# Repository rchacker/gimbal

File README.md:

gimbal
=======

Gimbal forked from _BruGi

Aim is to have a very simple 8 bit gimbal for which basic parameters are adjustable in the field without needing a computer.

*Agouti Prototype*

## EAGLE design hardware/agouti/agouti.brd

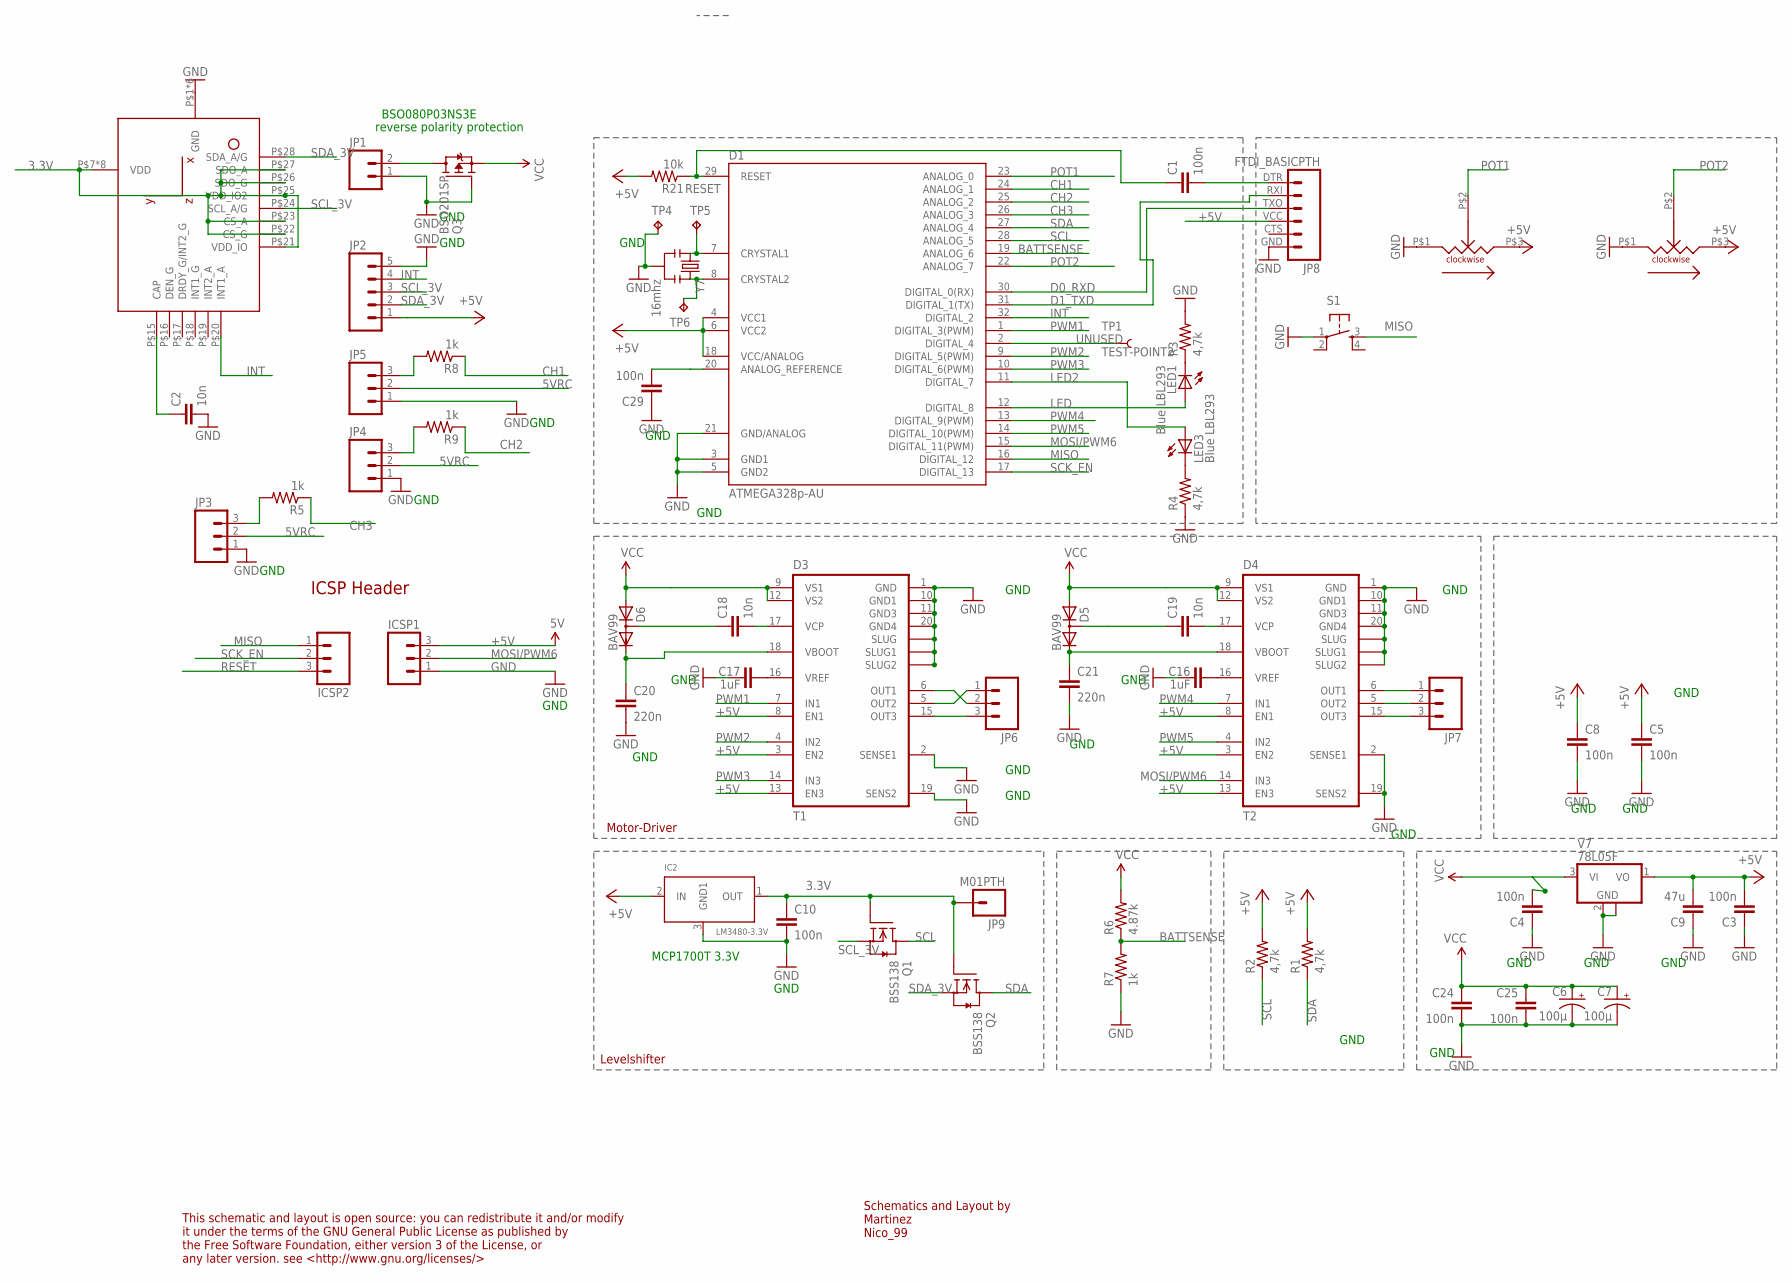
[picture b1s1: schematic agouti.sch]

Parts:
C1, C3, C4, C5, C8, C10, C24, C25, C29: 100n; 0805
C2, C18, C19: 10n; 0805
C6, C7: 100µ; PANASONIC_D
C9: 47u; C1210
C16, C17: 1uF; 0805
C20, C21: 220n; 0805
D1: ATMEGA328p-AU; TQFP32-08
D3: T1; SO20POWER2
D4: T2; SO20POWER2
D5, D6: BAV99; SOT23
IC2: LM3480-3.3V; SOT23
ICSP1, ICSP2: M03PTH; 1X03
JP1: M02PTH; 1X02
JP2: M05PTH; 1X05
JP3, JP4, JP5, JP6, JP7: M03PTH; 1X03
JP8: FTDI_BASICPTH; FTDI_BASIC
JP9: M01PTH; 1X01
LED1, LED3: Blue LBL293; CHIP-LED0603
Q1, Q2: BSS138; SOT23
Q3: BSO201SP; SO-8
R1, R2, R3, R4: 4,7k; 0805
R5, R7, R8, R9: 1k; 0805
R6: 4.87k; 0805
R21: 10k; 0805
S1: TAC_SWITCHSMD; TACTILE_SWITCH_SMD
TP1: TEST-POINT2; PAD.02X.02
TP4, TP5, TP6: TPTP06SQ; TP06SQ
U$3, U$5: TRIMMERPOT; BOURNES_3361P
U$6: LSM330; LGA-28
V7: 78L05F; SOT89
Y7: 16mhz; RESONATOR-SMD

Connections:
3.3V: C10.1, IC2.1 (OUT), JP9.1, Q1.1 (G), Q2.1 (G), U$6.P$7 (VDD), U$6.P$8 (VDD), U$6.P$9 (VDD), U$6.P$10 (VDD), U$6.P$11 (VDD), U$6.P$12 (VDD), U$6.P$13 (VDD), U$6.P$14 (VDD), U$6.P$21 (VDD_IO), U$6.P$22 (CS_G), U$6.P$23 (CS_A), U$6.P$25 (VDD_IO2), U$6.P$26 (SDO_G), U$6.P$27 (SDO_A)
5VRC: JP3.2, JP4.2, JP5.2
+5V: C3.2, C5.1, C8.1, C9.2, D1.4 (VCC1), D1.6 (VCC2), D1.18 (VCC/ANALOG), D3.3 (EN2), D3.8 (EN1), D3.13 (EN3), D4.3 (EN2), D4.8 (EN1), D4.13 (EN3), IC2.2 (IN), ICSP1.3, JP2.1, JP8.VCC (4), R1.2, R2.2, R21.2, U$3.P$3, U$5.P$3, V7.1 (VO)
BATTSENSE: D1.19 (ANALOG_6), R6.1, R7.2
CH1: D1.24 (ANALOG_1), R8.1
CH2: D1.25 (ANALOG_2), R9.1
CH3: D1.26 (ANALOG_3), R5.1
D0_RXD: D1.30 (DIGITAL_0(RX)), JP8.TXO (3)
D1_TXD: D1.31 (DIGITAL_1(TX)), JP8.RXI (2)
GND: C2.2, C3.1, C4.1, C5.2, C6.-, C7.-, C8.2, C9.1, C10.2, C16.1, C17.1, C20.2, C21.2, C24.2, C25.2, C29.1, D1.3 (GND1), D1.5 (GND2), D1.21 (GND/ANALOG), D3.1 (GND), D3.2 (SENSE1), D3.10 (GND1), D3.11 (GND3), D3.19 (SENS2), D3.20 (GND4), D3.SLUG (SLUG1), D3.SLUG1 (SLUG2), D3.SLUG2 (SLUG), D4.1 (GND), D4.2 (SENSE1), D4.10 (GND1), D4.11 (GND3), D4.19 (SENS2), D4.20 (GND4), D4.SLUG (SLUG1), D4.SLUG1 (SLUG2), D4.SLUG2 (SLUG), IC2.3 (GND1), ICSP1.1, JP1.1, JP2.5, JP3.1, JP4.1, JP5.1, JP8.GND (6), Q3.4 (G), R3.2, R4.1, R7.1, S1.1, TP4.TP, U$3.P$1, U$5.P$1, U$6.P$1 (GND), U$6.P$2 (GND), U$6.P$3 (GND), U$6.P$4 (GND), U$6.P$5 (GND), U$6.P$6 (GND), V7.2 (GND), V7.2@1 (GND), Y7.2
INT: D1.32 (DIGITAL_2), JP2.4, U$6.P$20 (INT1_A)
LED: D1.12 (DIGITAL_8), LED1.A
LED2: D1.11 (DIGITAL_7), LED3.A
MISO: D1.16 (DIGITAL_12), ICSP2.1, S1.3
MOSI/PWM6: D1.15 (DIGITAL_11(PWM)), D4.14 (IN3), ICSP1.2
unnamed: LED1.C, R3.1
unnamed: LED3.C, R4.2
unnamed: JP1.2, Q3.5 (D), Q3.6 (D), Q3.7 (D), Q3.8 (D)
unnamed: JP3.3, R5.2
unnamed: JP5.3, R8.2
unnamed: JP4.3, R9.2
unnamed: C16.2, D4.16 (VREF)
unnamed: C17.2, D3.16 (VREF)
unnamed: C1.2, JP8.DTR (1)
unnamed: C2.1, U$6.P$15 (CAP)
unnamed: C18.2, D3.17 (VCP)
unnamed: C19.2, D4.17 (VCP)
unnamed: C19.1, D5.3 (AC)
unnamed: C21.1, D4.18 (VBOOT), D5.2 (C)
unnamed: D3.15 (OUT3), JP6.3
unnamed: D4.6 (OUT1), JP7.1
unnamed: D4.5 (OUT2), JP7.2
unnamed: D4.15 (OUT3), JP7.3
unnamed: D3.5 (OUT2), JP6.1
unnamed: D3.6 (OUT1), JP6.2
unnamed: D1.8 (CRYSTAL2), TP6.TP, Y7.3
unnamed: D1.7 (CRYSTAL1), TP5.TP, Y7.1
unnamed: C29.2, D1.20 (ANALOG_REFERENCE)
POT1: D1.23 (ANALOG_0), U$3.P$2
POT2: D1.22 (ANALOG_7), U$5.P$2
PWM1: D1.1 (DIGITAL_3(PWM)), D3.7 (IN1)
PWM2: D1.9 (DIGITAL_5(PWM)), D3.4 (IN2)
PWM3: D1.10 (DIGITAL_6(PWM)), D3.14 (IN3)
PWM4: D1.13 (DIGITAL_9(PWM)), D4.7 (IN1)
PWM5: D1.14 (DIGITAL_10(PWM)), D4.4 (IN2)
RESET: C1.1, D1.29 (RESET), ICSP2.3, R21.1
SCK_EN: D1.17 (DIGITAL_13), ICSP2.2
SCL: D1.28 (ANALOG_5), Q1.3 (D), R2.1
SCL_3V: JP2.3, Q1.2 (S), U$6.P$24 (SCL_A/G)
SDA: D1.27 (ANALOG_4), Q2.3 (D), R1.1
SDA_3V: JP2.2, Q2.2 (S), U$6.P$28 (SDA_A/G)
UNUSED: D1.2 (DIGITAL_4), TP1.P$1
VBOOT1: C20.1, D3.18 (VBOOT), D6.2 (C)
VCC: C4.2, C6.+, C7.+, C24.1, C25.1, D3.9 (VS1), D3.12 (VS2), D4.9 (VS1), D4.12 (VS2), D5.1 (A), D6.1 (A), Q3.1 (S), Q3.2 (S), Q3.3 (S), R6.2, V7.3 (VI)
VCP1: C18.1, D6.3 (AC)

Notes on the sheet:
MCP1700T 3.3V
Motor-Driver
Levelshifter
This schematic and layout is open source: you can redistribute it and/or modify it under the terms of the GNU General Public License as published by the Free Software Foundation, either version 3 of the License, or any later version. see <http://www.gnu.org/licenses/>
Schematics and Layout by Martinez Nico_99
ICSP Header
GND
BSO080P03NS3E
reverse polarity protection

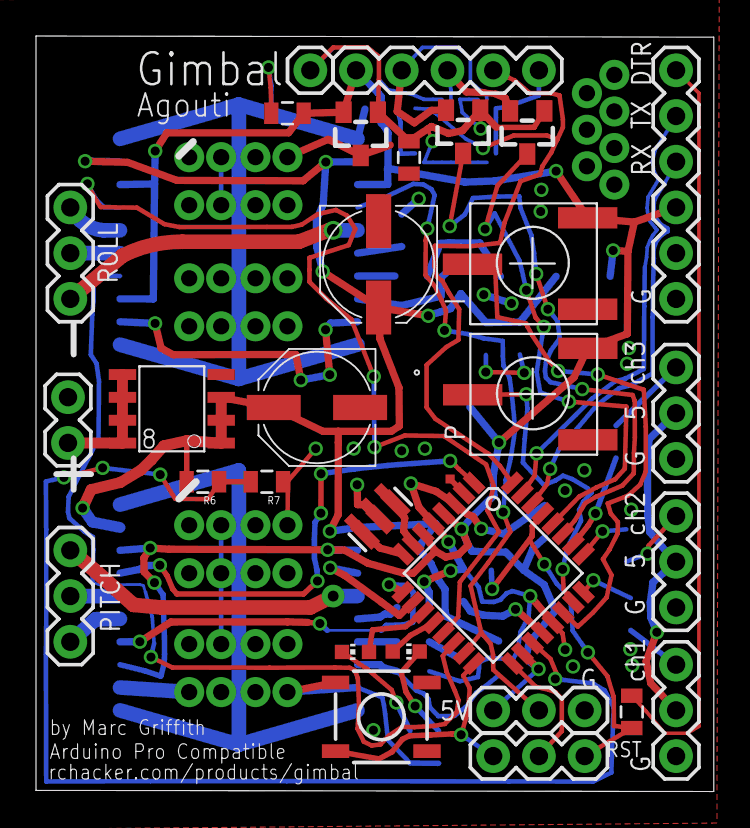
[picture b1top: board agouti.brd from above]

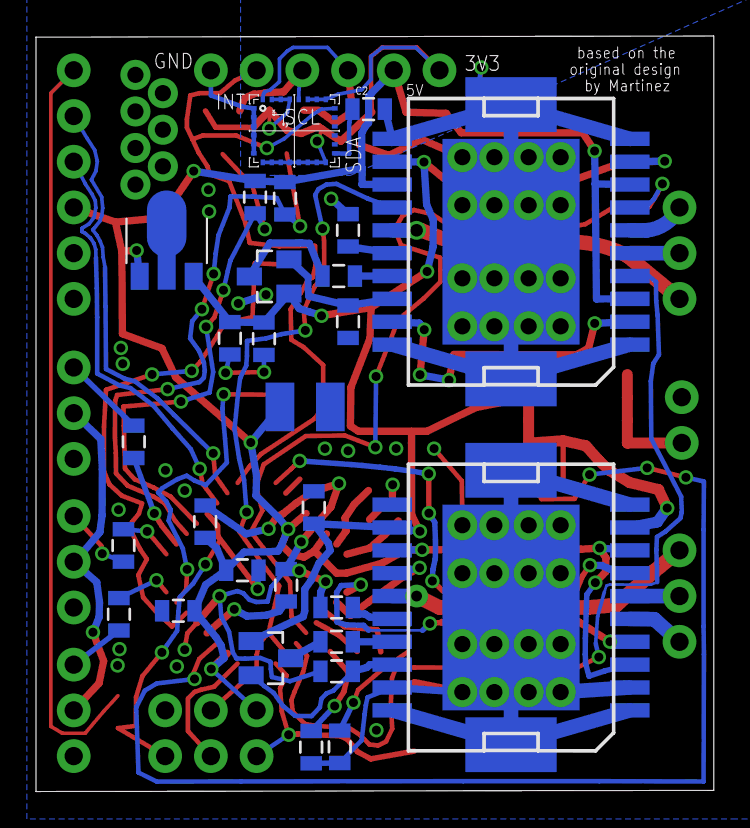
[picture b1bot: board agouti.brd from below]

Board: 2 copper layers, 37.7 x 42.0 mm, 62 parts (28 on the bottom side), 55 nets.

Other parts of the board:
U$2: RCHACKERLOGOBMP

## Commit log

2013-08-10 initial fork from https://code.google.com/p/brushless-gimbal/
2013-08-10 My hardware design that was based on martinez's
2013-08-11 hardware test sketches
2013-08-11 Pretty pictures.

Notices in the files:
parts and their libraries:
m-pad-2.1_my: License : GNU General Public License version 2 (see bottom)
SparkFun-Connectors: Licensing: CC v3.0 Share-Alike You are welcome to use this library for commercial purposes.
